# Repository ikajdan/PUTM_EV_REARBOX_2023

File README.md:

# Rearbox

This PCB integrates all rear-side vehicle electronics, handling communication, power outputs, and sensor inputs in a compact form factor.

<br>
<div align="center">
  </img>
  <br><br>
  <em>PCB layout.</em>
</div>
<br>

## Communication Interfaces

* **2× CAN transceivers** (external)
* **UART**, **SPI**, **I2C** (internal only)

## Power Outputs

* 2× fan drivers
* 2× pump drivers
* ASSI driver
* RTDS driver
* Brake light driver

## Sensor & Signal Inputs

* 12× digital safety inputs
* 2× suspension load cell sensors
* 2× suspension potentiometers
* 2× water pressure sensors
* 2× water temperature sensors
* Monocoque temperature sensors

## Overview

<br>
<div align="center">
  
&nbsp; &nbsp; &nbsp; &nbsp;
  
  <br><br>
  <em>Front and back view of the PCB.</em>
</div>
<br>

## Firmware

> [!IMPORTANT]
> For the CAN library to work correctly, the auto-generated HAL driver file needs to be patched.
>
> Make sure to restore any changes made by the generator to the `firmware/Drivers/STM32G4xx_HAL_Driver/Src/stm32g4xx_hal_fdcan.c` file or the receiving won't work!

Below are the changes that need to be made to the `stm32g4xx_hal_fdcan.c` file:

```diff
2231c2231
<     assert_param(IS_FDCAN_RX_FIFO(RxLocation));
---
>     //assert_param(IS_FDCAN_RX_FIFO(RxLocation));
2235c2235
<         if(RxLocation == FDCAN_RX_FIFO0) /* Rx element is assigned to the Rx FIFO 0 */
---
>         if(RxLocation == 0) /* Rx element is assigned to the Rx FIFO 0 */
2343c2343
<         if(RxLocation == FDCAN_RX_FIFO0) /* Rx element is assigned to the Rx FIFO 0 */
---
>         if(RxLocation == 0) /* Rx element is assigned to the Rx FIFO 0 */
```

## License

This project is licensed under the GPLv3 License. See the [LICENSE](LICENSE.md) file for details.

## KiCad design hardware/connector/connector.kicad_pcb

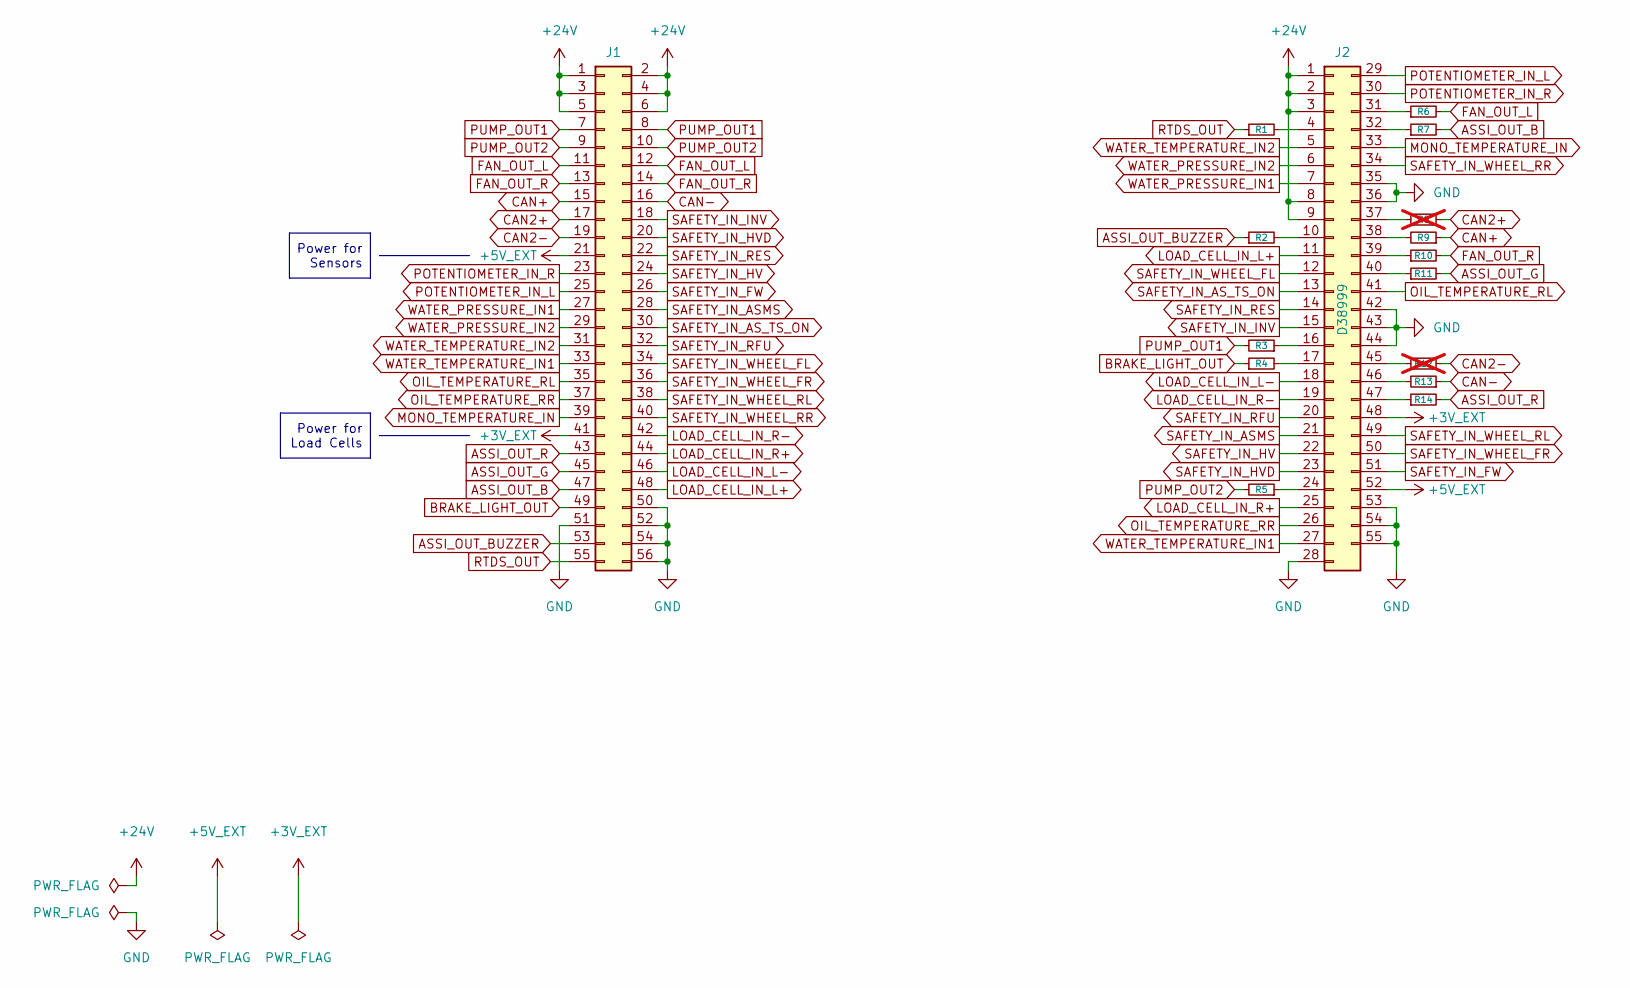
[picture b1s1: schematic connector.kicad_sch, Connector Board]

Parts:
J1: Conn_02x28_Top_Bottom; PinHeader_2x28_P2.00mm_Horizontal
J2: D38999; DTS20W17-35SN
R1, R2, R3, R4, R5, R6, R7, R9, R10, R11, R13, R14: 0R; R_0603_1608Metric
R8, R12: 0R; R_0603_1608Metric; not fitted

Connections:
+3V_EXT: J1.41, J2.48
+5V_EXT: J1.21, J2.52
+24V: J1.1, J1.2, J1.3, J1.4, J1.5, J1.6, J2.1, J2.2, J2.3, J2.8, J2.9
ASSI_OUT_B: J1.47, R7.2
ASSI_OUT_BUZZER: J1.53, R2.1
ASSI_OUT_G: J1.45, R11.2
ASSI_OUT_R: J1.43, R14.2
BRAKE_LIGHT_OUT: J1.49, R4.1
CAN2+: J1.17, R8.1
CAN2-: J1.19, R12.1
CAN+: J1.15, R9.1
CAN-: J1.16, R13.1
FAN_OUT_L: J1.11, J1.12, R6.2
FAN_OUT_R: J1.13, J1.14, R10.2
GND: J1.50, J1.51, J1.52, J1.54, J1.56, J2.28, J2.35, J2.36, J2.42, J2.43, J2.44, J2.53, J2.54, J2.55
LOAD_CELL_IN_L+: J1.48, J2.11
LOAD_CELL_IN_L-: J1.46, J2.18
LOAD_CELL_IN_R+: J1.44, J2.25
LOAD_CELL_IN_R-: J1.42, J2.19
MONO_TEMPERATURE_IN: J1.39, J2.33
unnamed: J2.4, R1.2
unnamed: J2.10, R2.2
unnamed: J2.16, R3.1
unnamed: J2.17, R4.2
unnamed: J2.24, R5.1
unnamed: J2.31, R6.1
unnamed: J2.32, R7.1
unnamed: J2.37, R8.2
unnamed: J2.38, R9.2
unnamed: J2.39, R10.1
unnamed: J2.40, R11.1
unnamed: J2.45, R12.2
unnamed: J2.46, R13.2
unnamed: J2.47, R14.1
OIL_TEMPERATURE_RL: J1.35, J2.41
OIL_TEMPERATURE_RR: J1.37, J2.26
POTENTIOMETER_IN_L: J1.25, J2.29
POTENTIOMETER_IN_R: J1.23, J2.30
PUMP_OUT1: J1.7, J1.8, R3.2
PUMP_OUT2: J1.9, J1.10, R5.2
RTDS_OUT: J1.55, R1.1
SAFETY_IN_ASMS: J1.28, J2.21
SAFETY_IN_AS_TS_ON: J1.30, J2.13
SAFETY_IN_FW: J1.26, J2.51
SAFETY_IN_HV: J1.24, J2.22
SAFETY_IN_HVD: J1.20, J2.23
SAFETY_IN_INV: J1.18, J2.15
SAFETY_IN_RES: J1.22, J2.14
SAFETY_IN_RFU: J1.32, J2.20
SAFETY_IN_WHEEL_FL: J1.34, J2.12
SAFETY_IN_WHEEL_FR: J1.36, J2.50
SAFETY_IN_WHEEL_RL: J1.38, J2.49
SAFETY_IN_WHEEL_RR: J1.40, J2.34
WATER_PRESSURE_IN1: J1.27, J2.7
WATER_PRESSURE_IN2: J1.29, J2.6
WATER_TEMPERATURE_IN1: J1.33, J2.27
WATER_TEMPERATURE_IN2: J1.31, J2.5

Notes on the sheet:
Power for Sensors
Power for Load Cells

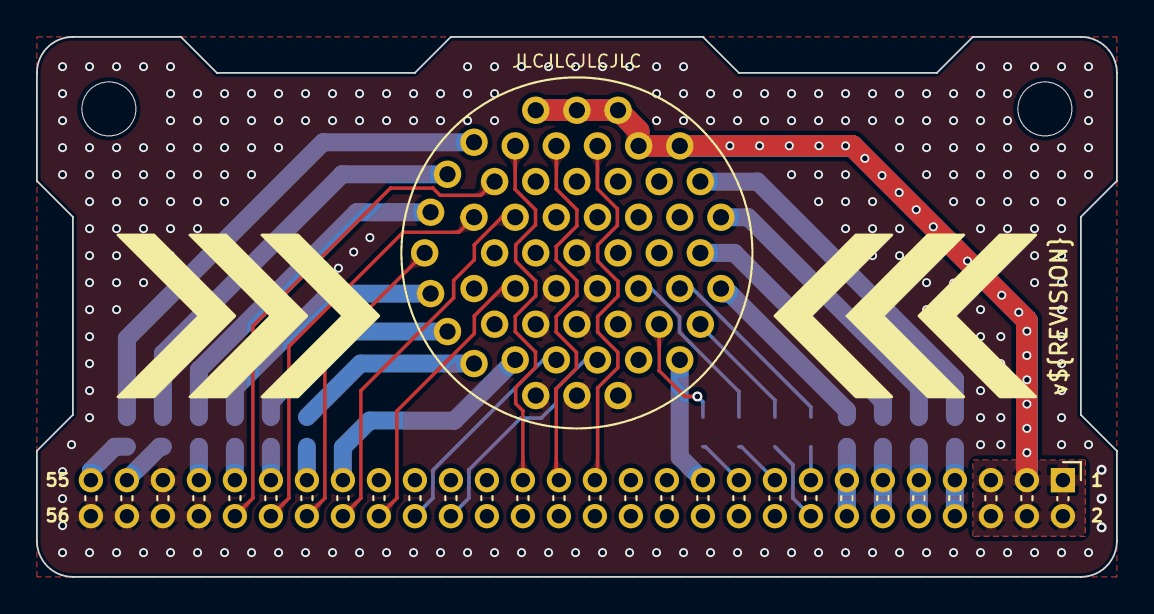
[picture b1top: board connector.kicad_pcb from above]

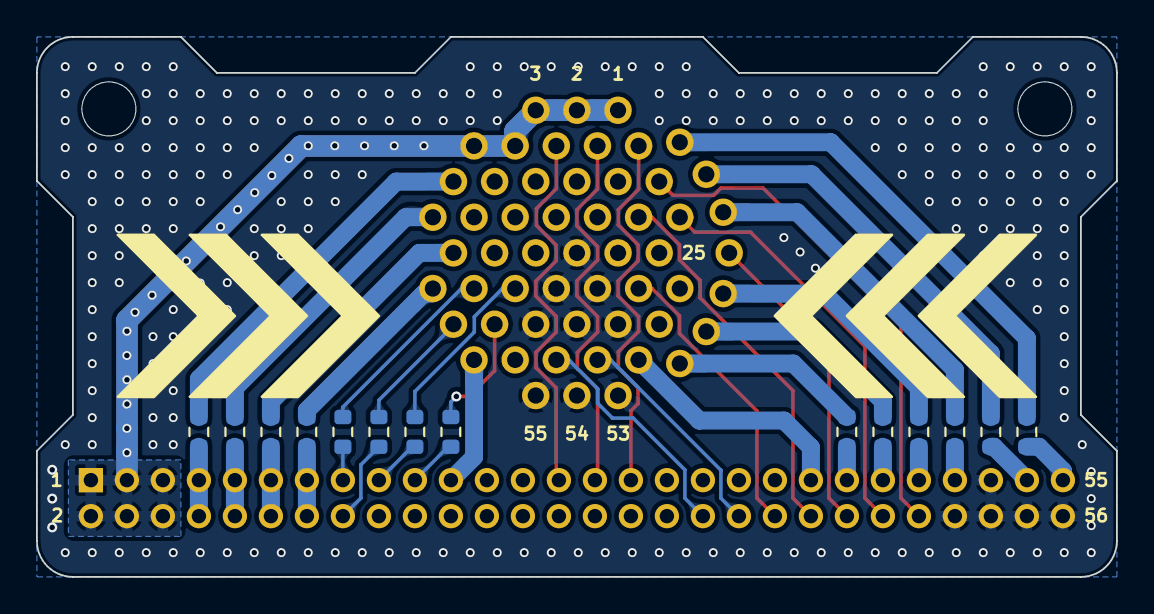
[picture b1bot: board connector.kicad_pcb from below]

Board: 4 copper layers, 60.0 x 30.0 mm, 16 parts (14 on the bottom side), 57 nets.

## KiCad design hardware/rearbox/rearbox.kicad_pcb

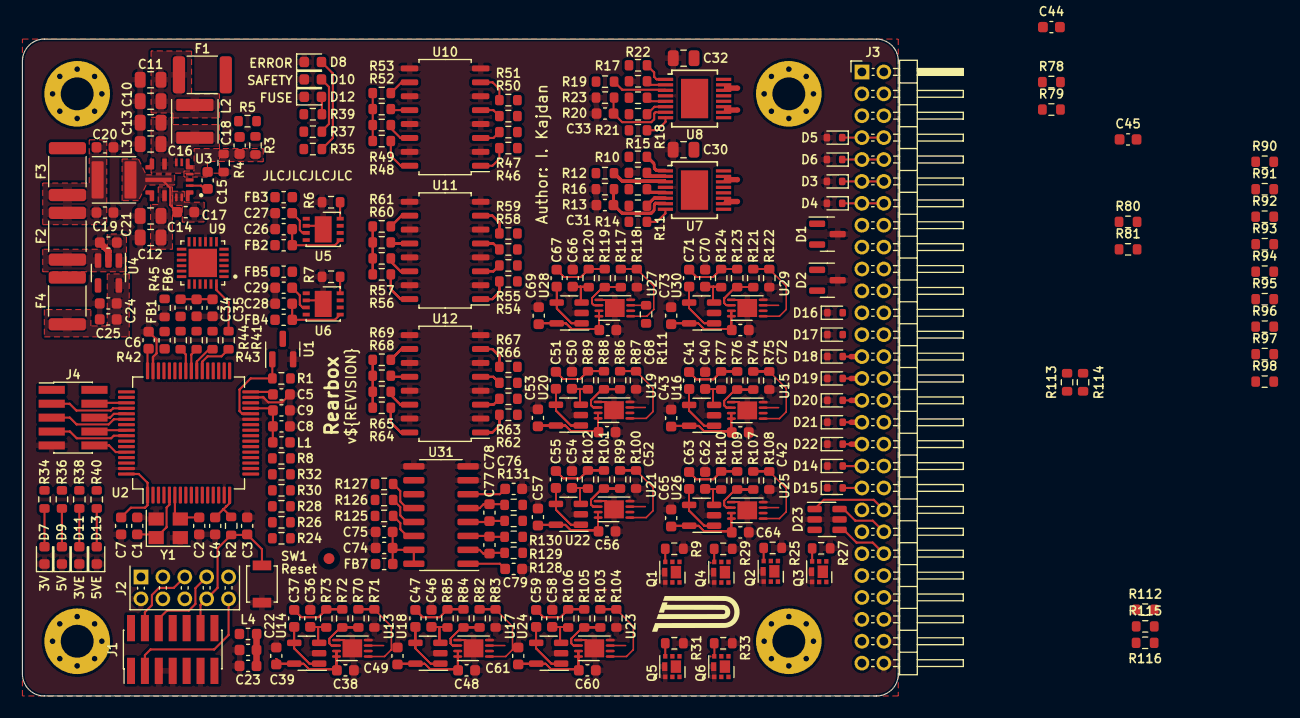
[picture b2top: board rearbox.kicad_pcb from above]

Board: 4 copper layers, 80.0 x 60.0 mm, 300 parts (0 on the bottom side), 227 nets.

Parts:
C1, C2: 10p; C_0603_1608Metric
C3, C4, C5, C6, C7, C9, C17, C23, C24, C26, C27, C28, C29, C35, C36, C37, C38, C39, C40, C41, C42, C43, C46, C47, C48, C49, C50, C51, C52, C53, C54, C55, C56, C57, C58, C59, C60, C61, C62, C63, C64, C65, C66, C67, C68, C69, C70, C71, C72, C73, C75, C76, C77, C78: 100n; C_0603_1608Metric
C8, C15, C21, C22, C25, C34, C74, C79: 1u; C_0603_1608Metric
C10, C11: 2u2; C_0805_2012Metric
C12, C13: 4u7; C_0805_2012Metric
C14, C16: 220n; C_0805_2012Metric
C18: 22p; C_0603_1608Metric
C19, C20: 22u; C_0603_1608Metric
C30, C32: 100n; C_0805_2012Metric
C31, C33, C44, C45: 10n; C_0603_1608Metric
D1, D2: PESD2CAN; SOT-23
D3, D4, D5, D6: PMEG3010EB; D_SOD-523
D7, D9, D11, D13: Green; LED_0603_1608Metric
D8, D10, D12: Red; LED_0603_1608Metric
D14, D15, D16, D17, D18, D19, D20, D21, D22: 5V; D_SOD-523
D23: CPDT6-5V4; SOT-23-6
F1: 1.5A; Fuse_1812_4532Metric
F2: 500mA; Fuse_1812_4532Metric
F3: 200mA; Fuse_1812_4532Metric
F4: 100mA; Fuse_1812_4532Metric
FB1, FB2, FB3, FB4, FB5, FB6, FB7: 470R; L_0603_1608Metric
J1: STDC14; PinHeader_2x07_P1.27mm_Vertical_SMD
J2: ST-LINK; STLINK-V3MINIE
J3: Conn_02x28_Top_Bottom; PinHeader_2x28_P2.00mm_Horizontal
J4: Auxiliary; PinHeader_2x05_P1.27mm_Vertical_SMD
L1, L4: 10u; L_0603_1608Metric
L2, L3: 1u5; L_Abracon_ASPI-4030S
NT1, NT2, NT3, NT4, NT5, NT6, NT7, NT8, NT9: NetTie_2; NetTie-2_SMD_Pad0.5mm
Q1, Q2, Q3, Q4, Q5, Q6: BUK6D210; Diodes_UDFN2020-6_Type-F
R1, R5, R90, R91, R92, R93, R95, R97: 1k; R_0603_1608Metric
R2, R9, R25, R27, R29, R31, R33, R48, R49, R52, R53, R56, R57, R60, R61, R64, R65, R68, R69: 10k; R_0603_1608Metric
R3: 100k; R_0603_1608Metric
R4: 24k9; R_0603_1608Metric
R6, R7, R45: 0R; R_0603_1608Metric
R8, R10, R11, R12, R13, R14, R17, R18, R19, R20, R21, R24, R26, R28, R30, R32, R41, R42, R43, R44, R79, R81, R125, R126, R127: 100R; R_0603_1608Metric
R15, R22: 15k; R_0603_1608Metric
R16, R23, R70, R71, R74, R75, R82, R83, R86, R87, R99, R100, R103, R104, R107, R108, R117, R118, R121, R122: TBD; R_0603_1608Metric
R34, R38: 82R; R_0603_1608Metric
R35, R37, R39: 120R; R_0603_1608Metric
R36, R40: 270R; R_0603_1608Metric
R46, R47, R50, R51, R54, R55, R58, R59, R62, R63, R66, R67: 2k; R_0603_1608Metric
R72, R73, R76, R77, R84, R85, R88, R89, R101, R102, R105, R106, R109, R110, R119, R120, R123, R124: 3k3; R_0603_1608Metric
R78, R80: 560R; R_0603_1608Metric
R94, R96, R98: 3k; R_0603_1608Metric
R111, R112, R113, R115: 50k; R_0603_1608Metric
R114, R116: 5k; R_0603_1608Metric
R128, R129, R130, R131: 51R; R_0603_1608Metric
SW1: Reset; SW_SPST_B3U-1000P
U1: LM4040C33FTA; SOT-23
U2: STM32G473RCTx; LQFP-64_10x10mm_P0.5mm
U3: LM62440-Q1; IC_LM61460AANRJRR
U4: TLV743P; SOT-23-5
U5, U6: MCP2542FD; DFN-8-1EP_3x3mm_P0.65mm_EP1.55x2.4mm
U7, U8: VND7020AJTR
U9: TCA6416ARTWR; QFN50P400X400X80-25N
U10, U11, U12: TLP291-4; SOIC-16_4.55x10.3mm_P1.27mm
U13, U15, U17, U19, U21, U23, U25, U27, U29: MCP6N11-005; TDFN-8-1EP_3x2mm_P0.5mm_EP1.80x1.65mm
U14, U16, U18, U20, U22, U24, U26, U28, U30: MCP6001; SOT-23-5
U31: NAU7802SGI; SOIC-16_3.9x9.9mm_P1.27mm
Y1: 48MHz; Crystal_SMD_Abracon_ABM8G-4Pin_3.2x2.5mm

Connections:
+3.3V: C24.1, C25.1, F4.1, FB1.2, FB2.1, FB4.1, FB6.1, FB7.1, J4.1, L1.1, L4.1, R34.1, R48.2, R49.2, R52.2, R53.2, R56.2, R57.2, R60.2, R61.2, R64.2, R65.2, R68.2, R69.2, U4.5 (OUT)
+3.3VA: C22.1, C23.1, C38.1, C39.1, C42.1, C43.1, C48.1, C49.1, C52.1, C53.1, C56.1, C57.1, C60.1, C61.1, C64.1, C65.1, C68.1, C69.1, C72.1, C73.1, L4.2, R78.1, R80.1, U13.7 (V+), U13.8 (EN), U14.5 (V+), U15.7 (V+), U15.8 (EN), U16.5 (V+), U17.7 (V+), U17.8 (EN), U18.5 (V+), U19.7 (V+), U19.8 (EN), U20.5 (V+), U21.7 (V+), U21.8 (EN), U22.5 (V+), U23.7 (V+), U23.8 (EN), U24.5 (V+), U25.7 (V+), U25.8 (EN), U26.5 (V+), U27.7 (V+), U27.8 (EN), U28.5 (V+), U29.7 (V+), U29.8 (EN), U30.5 (V+)
+3V_EXT: C79.1, F4.2, J3.41, R38.1, U31.1 (REFP)
+5V: C19.1, C20.1, F2.1, F3.1, FB3.1, FB5.1, J4.2, L3.2, R1.1, R3.1, R5.1, R36.1, U3.1 (BIAS)
+5V_EXT: F3.2, J3.21, R40.1, R90.1, R91.1, R92.1, R93.1, R95.1, R97.1, R111.1, R112.1, R113.1, R115.1
+24V: C30.1, C32.1, F1.1, J3.1, J3.2, J3.3, J3.4, J3.5, J3.6, U7.EPAD (VCC), U8.EPAD (VCC)
/ANALOG_INPUT1: C37.2, U2.20 (PA6), U14.1, U14.4 (-)
/ANALOG_INPUT2: C41.2, U2.21 (PA7), U16.1, U16.4 (-)
/ANALOG_OFFSET1: U2.18 (PA4), U13.2 (-)
/ANALOG_OFFSET2: U2.19 (PA5), U15.2 (-)
/ASSI_BUZZER: R30.2, U2.4 (PC15)
/ASSI_LED_B: R28.2, U2.17 (PA3)
/ASSI_LED_G: R26.2, U2.9 (PC1)
/ASSI_LED_R: R24.2, U2.8 (PC0)
/BRAKE_LIGHT: R8.2, U2.2 (PC13)
/CAN2_RX: U2.34 (PB12), U6.4 (RXD)
/CAN2_TX: U2.35 (PB13), U6.1 (TXD)
/CAN_RX: U2.45 (PA11), U5.4 (RXD)
/CAN_TX: U2.46 (PA12), U5.1 (TXD)
/FAN_L: R10.1, U2.37 (PB15)
/FAN_R: R11.1, U2.36 (PB14)
/HSE_IN: C1.1, U2.5 (PF0), Y1.1
/HSE_OUT: C2.1, U2.6 (PF1), Y1.3
/LED_ERROR: R35.1, U9.6 (P05)
/LED_FUSE: R39.1, U9.8 (P07)
/LED_SAFETY: R37.1, U9.7 (P06)
/LOAD_CELL_DRDY: R127.1, U2.44 (PA10)
/LOAD_CELL_SCLK: R126.1, U2.43 (PA9)
/LOAD_CELL_SDIO: R125.1, U2.42 (PA8)
/MONO_TEMPERATURE: C63.2, U2.10 (PC2), U26.1, U26.4 (-)
/POTENTIOMETER_L: C67.2, U2.22 (PC4), U28.1, U28.4 (-)
/POTENTIOMETER_R: C71.2, U2.23 (PC5), U30.1, U30.4 (-)
/PUMP1: R17.1, U2.33 (PB11)
/PUMP2: R18.1, U2.30 (PB10)
/Power Supply/+5V_FUSED: C21.1, F2.2, U4.1 (IN), U4.3 (EN)
/Power Supply/+24V_FUSED: C10.1, C11.1, F1.2, L2.1
/Power Supply/FB: C18.2, R3.2, R4.1, U3.4 (FB)
/Power Supply/SW: C17.1, L3.1, U3.10 (SW)
/Power Supply/VIN: C12.1, C13.1, C14.1, C16.1, L2.2, U3.7 (EN), U3.8 (VIN1), U3.12 (VIN2)
/RTDS: R32.2, U2.3 (PC14)
/SAFETY_SCL: R43.1, U2.40 (PC8)
/SAFETY_SDA: R42.1, U2.41 (PC9)
/SAFETY_~INT: R44.1, U2.39 (PC7)
/SAFETY_~RESET: R41.1, U2.38 (PC6)
/SENSE_ADDRESS_IN0: R13.1, R20.1, U2.25 (PB1)
/SENSE_ADDRESS_IN1: R14.1, R21.1, U2.26 (PB2)
/SENSE_ENABLE_FANS: R12.1, U2.59 (PB6)
/SENSE_ENABLE_PUMPS: R19.1, U2.58 (PB5)
/SENSE_OUT: C31.1, C33.1, R16.1, R23.1, U2.24 (PB0), U7.7 (MultiSense), U8.7 (MultiSense)
/Safety Inputs/OUT_ASMS: R65.1, U9.15, U12.14
/Safety Inputs/OUT_FW: R48.1, U9.1 (P00), U10.16
/Safety Inputs/OUT_HV: R49.1, U9.2 (P01), U10.14
/Safety Inputs/OUT_HVD: R53.1, U9.4 (P03), U10.10
/Safety Inputs/OUT_INV: R52.1, U9.3 (P02), U10.12
/Safety Inputs/OUT_RES: R64.1, U9.14, U12.16
/Safety Inputs/OUT_RFU1: R68.1, U9.16, U12.12
/Safety Inputs/OUT_RFU2: R69.1, U9.17, U12.10
/Safety Inputs/OUT_W_FL: R56.1, U9.10, U11.16
/Safety Inputs/OUT_W_FR: R57.1, U9.11, U11.14
/Safety Inputs/OUT_W_RL: R60.1, U9.12, U11.12
/Safety Inputs/OUT_W_RR: R61.1, U9.13, U11.10
/Safety Inputs/TCA_VDD: C34.1, C35.1, FB6.2, U9.21 (VCCP), U9.23 (VCCI)
/Suspension Load Cells/NAU_VDD: C74.1, C75.1, FB7.2, U31.15 (DVDD), U31.16 (AVDD)
/Suspension Potentiometers/N1: R113.2, R114.1, U27.2 (-)
/Suspension Potentiometers/N2: R115.2, R116.1, U29.2 (-)
/Suspension Potentiometers/P1: D21.2 (A2), NT8.2, R111.2, U27.3 (+)
/Suspension Potentiometers/P2: D22.2 (A2), NT9.2, R112.2, U29.3 (+)
/Temperature Sensors/N1: R93.2, R94.1, U21.2 (-)
/Temperature Sensors/N2: R95.2, R96.1, U23.2 (-)
/Temperature Sensors/N3: R97.2, R98.1, U25.2 (-)
/Temperature Sensors/P1: D18.2 (A2), NT5.2, R90.2, U21.3 (+)
/Temperature Sensors/P2: D19.2 (A2), NT6.2, R91.2, U23.3 (+)
/Temperature Sensors/P3: D20.2 (A2), NT7.2, R92.2, U25.3 (+)
/VREF: R1.2, U1.1 (K), U2.28 (VREF+)
/WATER_PRESSURE1: C47.2, U2.13 (PA1), U18.1, U18.4 (-)
/WATER_PRESSURE2: C51.2, U2.14 (PA2), U20.1, U20.4 (-)
/WATER_TEMPERATURE1: C55.2, U2.11 (PC3), U22.1, U22.4 (-)
/WATER_TEMPERATURE2: C59.2, U2.12 (PA0), U24.1, U24.4 (-)
/Water Pressure Sensors/Analog Input 3/-: C44.1, R78.2, R79.1, U17.2 (-)
/Water Pressure Sensors/Analog Input 4/-: C45.1, R80.2, R81.1, U19.2 (-)
ANALOG_IN_RFU1: D14.2 (A2), J3.37, U13.3 (+)
ANALOG_IN_RFU2: D15.2 (A2), J3.39, U15.3 (+)
ASSI_OUT_B: J3.47, Q4.1 (D), Q4.2 (D), Q4.5 (D), Q4.6 (D), Q4.7 (D)
ASSI_OUT_BUZZER: J3.53, Q5.1 (D), Q5.2 (D), Q5.5 (D), Q5.6 (D), Q5.7 (D)
ASSI_OUT_G: J3.45, Q3.1 (D), Q3.2 (D), Q3.5 (D), Q3.6 (D), Q3.7 (D)
ASSI_OUT_R: J3.43, Q2.1 (D), Q2.2 (D), Q2.5 (D), Q2.6 (D), Q2.7 (D)
BRAKE_LIGHT_OUT: J3.49, Q1.1 (D), Q1.2 (D), Q1.5 (D), Q1.6 (D), Q1.7 (D)
CAN2+: D2.1 (A1), J3.17, U6.7 (CANH)
CAN2-: D2.2 (A2), J3.19, U6.6 (CANL)
CAN+: D1.1 (A1), J3.15, U5.7 (CANH)
CAN-: D1.2 (A2), J3.16, U5.6 (CANL)
FAN_OUT_L: D3.1 (K), J3.11, J3.12, NT1.1, NT1.2, U7.13 (OUTPUT0), U7.14 (OUTPUT0), U7.15 (OUTPUT0), U7.16 (OUTPUT0)
FAN_OUT_R: D4.1 (K), J3.13, J3.14, NT2.1, NT2.2, U7.9 (OUTPUT1), U7.10 (OUTPUT1), U7.11 (OUTPUT1), U7.12 (OUTPUT1)
GND: C1.2, C2.2, C3.2, C4.2, C5.2, C6.2, C7.2, C8.2, C9.2, C10.2, C11.2, C12.2, C13.2, C14.2, C15.2, C16.2, C19.2, C20.2, C21.2, C22.2, C23.2, C24.2, C25.2, C26.2, C27.2, C28.2, C29.2, C30.2, C31.2, C32.2, C33.2, C34.2, C35.2, C36.2, C38.2, C39.2, C40.2, C42.2, C43.2, C44.2, C45.2, C46.2, C48.2, C49.2, C50.2, C52.2, C53.2, C54.2, C56.2, C57.2, C58.2, C60.2, C61.2, C62.2, C64.2, C65.2, C66.2, C68.2, C69.2, C70.2, C72.2, C73.2, C74.2, C75.2, C76.2, C79.2, D1.3 (common), D2.3 (common), D3.2 (A), D4.2 (A), D5.2 (A), D6.2 (A), D7.1 (K), D8.1 (K), D9.1 (K), D10.1 (K), D11.1 (K), D12.1 (K), D13.1 (K), D14.1 (A1), D15.1 (A1), D16.1 (A1), D17.1 (A1), D18.1 (A1), D19.1 (A1), D20.1 (A1), D21.1 (A1), D22.1 (A1), D23.2 (D2), D23.5 (A5), J1.5, J1.7, J1.11, J2.6 (GND), J3.50, J3.51, J3.52, J3.54, J3.56, J4.9, Q1.4 (S), Q1.8 (S), Q2.4 (S), Q2.8 (S), Q3.4 (S), Q3.8 (S), Q4.4 (S), Q4.8 (S), Q5.4 (S), Q5.8 (S), Q6.4 (S), Q6.8 (S), R4.2, R6.1, R7.1, R9.1, R15.2, R16.2, R22.2, R23.2, R25.1, R27.1, R29.1, R31.1, R33.1, R45.1, R71.1, R75.1, R79.2, R81.2, R83.1, R87.1, R94.2, R96.2, R98.2, R100.1, R104.1, R108.1, R114.2, R116.2, R118.1, R122.1, SW1.1, U1.2 (A), U2.15 (VSS), U2.27 (VSSA), U2.31 (VSS), U2.47 (VSS), U2.63 (VSS), U3.3 (AGND), U3.6 (MODE/SYNC), U3.9 (PGND1), U3.11 (PGND2), U4.2 (GND), U5.2 (VSS), U5.9 (VSS), U6.2 (VSS), U6.9 (VSS), U7.4 (GND), U8.4 (GND), U9.9 (GND), U9.25 (EP), U10.2, U10.4, U10.6, U10.8, U10.9, U10.11, U10.13, U10.15, U11.2, U11.4, U11.6, U11.8, U11.9, U11.11, U11.13, U11.15, U12.2, U12.4, U12.6, U12.8, U12.9, U12.11, U12.13, U12.15, U13.4 (V-), U13.5 (RF), U13.9 (EP), U14.2 (V-), U15.4 (V-), U15.5 (RF), U15.9 (EP), U16.2 (V-), U17.4 (V-), U17.5 (RF), U17.9 (EP), U18.2 (V-), U19.4 (V-), U19.5 (RF), U19.9 (EP), U20.2 (V-), U21.4 (V-), U21.5 (RF), U21.9 (EP), U22.2 (V-), U23.4 (V-), U23.5 (RF), U23.9 (EP), U24.2 (V-), U25.4 (V-), U25.5 (RF), U25.9 (EP), U26.2 (V-), U27.4 (V-), U27.5 (RF), U27.9 (EP), U28.2 (V-), U29.4 (V-), U29.5 (RF), U29.9 (EP), U30.2 (V-), U31.7 (REFN), U31.8 (AVSS), U31.9 (DVSS), Y1.2, Y1.4
I^{2}C_SCL: J4.4, U2.51 (PA15)
I^{2}C_SDA: J4.10, U2.60 (PB7)
LOAD_CELL_IN_L+: D23.1 (A1), J3.42, R128.2
LOAD_CELL_IN_L-: D23.6 (D6), J3.44, R129.2
LOAD_CELL_IN_R+: D23.4 (C4), J3.46, R130.2
LOAD_CELL_IN_R-: D23.3 (B3), J3.48, R131.2
MONO_TEMPERATURE_IN: J3.31, NT7.1
NRST: C3.1, J1.12, J2.9 (T_NRST), R2.2, SW1.2, U2.7 (PG10)
unnamed: C18.1, R5.2
unnamed: C37.1, R72.2, R73.1
unnamed: C41.1, R76.2, R77.1
unnamed: C47.1, R84.2, R85.1
unnamed: C51.1, R88.2, R89.1
unnamed: C55.1, R101.2, R102.1
unnamed: C59.1, R105.2, R106.1
unnamed: C63.1, R109.2, R110.1
unnamed: C67.1, R119.2, R120.1
unnamed: C71.1, R123.2, R124.1
unnamed: D7.2 (A), R34.2
unnamed: D8.2 (A), R35.2
unnamed: D9.2 (A), R36.2
unnamed: D10.2 (A), R37.2
unnamed: D11.2 (A), R38.2
unnamed: D12.2 (A), R39.2
unnamed: D13.2 (A), R40.2
unnamed: Q1.3 (G), R8.1, R9.2
unnamed: Q2.3 (G), R24.1, R25.2
unnamed: Q3.3 (G), R26.1, R27.2
unnamed: Q4.3 (G), R28.1, R29.2
unnamed: Q5.3 (G), R30.1, R31.2
unnamed: Q6.3 (G), R32.1, R33.2
unnamed: R46.2, U10.1
unnamed: R47.2, U10.3
unnamed: R50.2, U10.5
unnamed: R51.2, U10.7
unnamed: R54.2, U11.1
unnamed: R55.2, U11.3
unnamed: R58.2, U11.5
unnamed: R59.2, U11.7
unnamed: R62.2, U12.1
unnamed: R63.2, U12.3
unnamed: R66.2, U12.5
unnamed: R67.2, U12.7
unnamed: R70.2, R72.1, U13.6
unnamed: R74.2, R76.1, U15.6
unnamed: R82.2, R84.1, U17.6
unnamed: R86.2, R88.1, U19.6
unnamed: R99.2, R101.1, U21.6
unnamed: R103.2, R105.1, U23.6
unnamed: R107.2, R109.1, U25.6
unnamed: R117.2, R119.1, U27.6
unnamed: R121.2, R123.1, U29.6
unnamed: C17.2, U3.13 (RBOOT), U3.14 (CBOOT)
unnamed: C15.1, U3.2 (VCC)
unnamed: R6.2, U5.8 (STBY)
unnamed: C27.1, FB3.2, U5.3 (VDD)
unnamed: C26.1, FB2.2, U5.5 (VIO)
unnamed: R7.2, U6.8 (STBY)
unnamed: C29.1, FB5.2, U6.3 (VDD)
unnamed: C28.1, FB4.2, U6.5 (VIO)
unnamed: R10.2, U7.1 (INPUT0)
unnamed: R11.2, U7.8 (INPUT1)
unnamed: R13.2, U7.5 (SEL0)
unnamed: R14.2, U7.6 (SEL1)
unnamed: R12.2, U7.3 (SEn)
unnamed: R15.1, U7.2 (~FaultRST)
unnamed: R17.2, U8.1 (INPUT0)
unnamed: R18.2, U8.8 (INPUT1)
unnamed: R20.2, U8.5 (SEL0)
unnamed: R21.2, U8.6 (SEL1)
unnamed: R19.2, U8.3 (SEn)
unnamed: R22.1, U8.2 (~FaultRST)
unnamed: R45.2, U9.18 (ADDR)
unnamed: R43.2, U9.19 (SCL)
unnamed: R42.2, U9.20 (SDA)
unnamed: R44.2, U9.22 (~INT)
unnamed: R41.2, U9.24 (~RESET)
unnamed: R70.1, R71.2, U13.1 (FG)
unnamed: C36.1, R73.2, U14.3 (+)
unnamed: R74.1, R75.2, U15.1 (FG)
unnamed: C40.1, R77.2, U16.3 (+)
unnamed: R82.1, R83.2, U17.1 (FG)
unnamed: C46.1, R85.2, U18.3 (+)
unnamed: R86.1, R87.2, U19.1 (FG)
unnamed: C50.1, R89.2, U20.3 (+)
unnamed: R99.1, R100.2, U21.1 (FG)
unnamed: C54.1, R102.2, U22.3 (+)
unnamed: R103.1, R104.2, U23.1 (FG)
unnamed: C58.1, R106.2, U24.3 (+)
unnamed: R107.1, R108.2, U25.1 (FG)
unnamed: C62.1, R110.2, U26.3 (+)
unnamed: R117.1, R118.2, U27.1 (FG)
unnamed: C66.1, R120.2, U28.3 (+)
unnamed: R121.1, R122.2, U29.1 (FG)
unnamed: C70.1, R124.2, U30.3 (+)
unnamed: R127.2, U31.12 (DRDY)
unnamed: R126.2, U31.13 (SCLK)
unnamed: R125.2, U31.14 (SDIO)
unnamed: C76.1, U31.6 (VBG)
unnamed: C77.1, R128.1, U31.2 (VIN1N)
unnamed: C77.2, R129.1, U31.3 (VIN1P)
unnamed: C78.1, R130.1, U31.4 (VIN2N)
unnamed: C78.2, R131.1, U31.5 (VIN2P)
POTENTIOMETER_IN_L: J3.33, NT8.1
POTENTIOMETER_IN_R: J3.35, NT9.1
PUMP_OUT1: D5.1 (K), J3.7, J3.8, NT3.1, NT3.2, U8.13 (OUTPUT0), U8.14 (OUTPUT0), U8.15 (OUTPUT0), U8.16 (OUTPUT0)
PUMP_OUT2: D6.1 (K), J3.9, J3.10, NT4.1, NT4.2, U8.9 (OUTPUT1), U8.10 (OUTPUT1), U8.11 (OUTPUT1), U8.12 (OUTPUT1)
RTDS_OUT: J3.55, Q6.1 (D), Q6.2 (D), Q6.5 (D), Q6.6 (D), Q6.7 (D)
SAFETY_IN_ASMS: J3.28, R63.1
SAFETY_IN_FW: J3.26, R46.1
SAFETY_IN_HV: J3.24, R47.1
SAFETY_IN_HVD: J3.20, R51.1
SAFETY_IN_INV: J3.18, R50.1
SAFETY_IN_RES: J3.22, R62.1
SAFETY_IN_RFU1: J3.30, R66.1
SAFETY_IN_RFU2: J3.32, R67.1
SAFETY_IN_WHEEL_FL: J3.34, R54.1
SAFETY_IN_WHEEL_FR: J3.36, R55.1
SAFETY_IN_WHEEL_RL: J3.38, R58.1
SAFETY_IN_WHEEL_RR: J3.40, R59.1
SPI_MISO: J4.7, U2.57 (PB4)
SPI_MOSI: J4.5, U2.54 (PC12)
SPI_SCLK: J4.8, U2.56 (PB3)
SWCLK: J1.6, J2.4 (T_JCLK/T_SWCLK), U2.50 (PA14)
SWDIO: J1.4, J2.3 (T_JTMS/T_SWDIO), U2.49 (PA13)
UART_RX: J4.6, U2.53 (PC11)
UART_TX: J4.3, U2.52 (PC10)
VDD: C4.1, C5.1, C6.1, C7.1, FB1.1, J1.3, J2.10 (T_VCC), R2.1, U2.1 (VBAT), U2.16 (VDD), U2.32 (VDD), U2.48 (VDD), U2.64 (VDD)
VDDA: C8.1, C9.1, L1.2, U2.29 (VDDA)
WATER_PRESSURE_IN1: D16.2 (A2), J3.23, U17.3 (+)
WATER_PRESSURE_IN2: D17.2 (A2), J3.25, U19.3 (+)
WATER_TEMPERATURE_IN1: J3.27, NT5.1
WATER_TEMPERATURE_IN2: J3.29, NT6.1

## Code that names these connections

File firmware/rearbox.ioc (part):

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Mcu.Name=STM32G473R(B-C-E)Tx
Mcu.Package=LQFP64
Mcu.UserName=STM32G473RCTx
PA0.GPIOParameters=GPIO_Label
PA0.GPIO_Label=WATER_TEMPERATURE2
PA0.Mode=IN1-Single-Ended
PA0.Signal=ADC1_IN1
PA1.GPIOParameters=GPIO_Label
PA1.GPIO_Label=WATER_PRESSURE1
PA1.Mode=IN2-Single-Ended
PA1.Signal=ADC1_IN2
PA10.GPIOParameters=GPIO_Label
PA10.GPIO_Label=LOAD_CELL_DRDY
PA10.Signal=GPXTI10
PA11.GPIOParameters=GPIO_Label
PA11.GPIO_Label=CAN_RX
PA11.Mode=FDCAN_Activate
PA11.Signal=FDCAN1_RX
PA12.GPIOParameters=GPIO_Label
PA12.GPIO_Label=CAN_TX
PA12.Mode=FDCAN_Activate
PA12.Signal=FDCAN1_TX
PA13.GPIOParameters=GPIO_Label
PA13.GPIO_Label=SWDIO
PA13.Mode=Serial_Wire
PA13.Signal=SYS_JTMS-SWDIO
PA14.GPIOParameters=GPIO_Label
PA14.GPIO_Label=SWCLK
PA14.Mode=Serial_Wire
PA14.Signal=SYS_JTCK-SWCLK
PA15.GPIOParameters=GPIO_Label
PA15.GPIO_Label=I2C_SCL
PA15.Mode=I2C
PA15.Signal=I2C1_SCL
PA2.GPIOParameters=GPIO_Label
PA2.GPIO_Label=WATER_PRESSURE2
PA2.Mode=IN3-Single-Ended
PA2.Signal=ADC1_IN3
PA3.GPIOParameters=GPIO_Label
PA3.GPIO_Label=ASSI_LED_B
PA3.Signal=GPIO_Output
PA4.GPIOParameters=GPIO_Label
PA4.GPIO_Label=ANALOG_OFFSET1
PA4.Signal=COMP_DAC11_group
PA5.GPIOParameters=GPIO_Label
PA5.GPIO_Label=ANALOG_OFFSET2
PA5.Signal=COMP_DAC12_group
PA6.GPIOParameters=GPIO_Label
PA6.GPIO_Label=ANALOG_INPUT1
PA6.Mode=IN3-Single-Ended
PA6.Signal=ADC2_IN3
PA7.GPIOParameters=GPIO_Label
PA7.GPIO_Label=ANALOG_INPUT2
PA7.Mode=IN4-Single-Ended
PA7.Signal=ADC2_IN4
PA8.GPIOParameters=GPIO_Label
PA8.GPIO_Label=LOAD_CELL_SDIO
PA8.Mode=I2C
PA8.Signal=I2C2_SDA
PA9.GPIOParameters=GPIO_Label
PA9.GPIO_Label=LOAD_CELL_SCLK
PA9.Mode=I2C
PA9.Signal=I2C2_SCL
PB0.GPIOParameters=GPIO_Label
PB0.GPIO_Label=SENSE_OUT
PB0.Mode=IN15-Single-Ended
PB0.Signal=ADC1_IN15
PB1.GPIOParameters=GPIO_Label
PB1.GPIO_Label=SENSE_ADDRESS_IN0
PB1.Signal=GPIO_Output
PB10.GPIOParameters=GPIO_Label
PB10.GPIO_Label=PUMP2
PB10.Signal=S_TIM2_CH3
PB11.GPIOParameters=GPIO_Label
PB11.GPIO_Label=PUMP1
PB11.Signal=S_TIM2_CH4
PB12.GPIOParameters=GPIO_Label
PB12.GPIO_Label=CAN2_RX
PB12.Signal=FDCAN2_RX
PB13.GPIOParameters=GPIO_Label
PB13.GPIO_Label=CAN2_TX
PB13.Signal=FDCAN2_TX
PB14.GPIOParameters=GPIO_Label
PB14.GPIO_Label=FAN_R
PB14.Signal=S_TIM15_CH1
PB15.GPIOParameters=GPIO_Label
PB15.GPIO_Label=FAN_L
PB15.Signal=S_TIM15_CH2
PB2.GPIOParameters=GPIO_Label
PB2.GPIO_Label=SENSE_ADDRESS_IN1
PB2.Signal=GPIO_Output
PB3.GPIOParameters=GPIO_Label
PB3.GPIO_Label=SPI_SCLK
PB3.Mode=Full_Duplex_Master
PB3.Signal=SPI3_SCK
PB4.GPIOParameters=GPIO_Label
PB4.GPIO_Label=SPI_MISO
PB4.Mode=Full_Duplex_Master
PB4.Signal=SPI3_MISO
PB5.GPIOParameters=GPIO_Label
PB5.GPIO_Label=SENSE_ENABLE_PUMPS
PB5.Signal=GPIO_Output
PB6.GPIOParameters=GPIO_Label
PB6.GPIO_Label=SENSE_ENABLE_FANS
PB6.Signal=GPIO_Output
PB7.GPIOParameters=GPIO_Label
PB7.GPIO_Label=I2C_SDA
PB7.Mode=I2C
PB7.Signal=I2C1_SDA
PB8-BOOT0.GPIOParameters=GPIO_Label
PB8-BOOT0.GPIO_Label=BOOT_SELECT
PB8-BOOT0.Signal=GPIO_Output
PC0.GPIOParameters=GPIO_Label
PC0.GPIO_Label=ASSI_LED_R
PC0.Signal=GPIO_Output
PC1.GPIOParameters=GPIO_Label
PC1.GPIO_Label=ASSI_LED_G
PC1.Signal=GPIO_Output
PC10.GPIOParameters=GPIO_Label
PC10.GPIO_Label=UART_TX
PC10.Mode=Asynchronous
PC10.Signal=USART3_TX
PC11.GPIOParameters=GPIO_Label
PC11.GPIO_Label=UART_RX
PC11.Mode=Asynchronous
PC11.Signal=USART3_RX
PC12.GPIOParameters=GPIO_Label
PC12.GPIO_Label=SPI_MOSI
PC12.Mode=Full_Duplex_Master
PC12.Signal=SPI3_MOSI
PC13.GPIOParameters=GPIO_Label
PC13.GPIO_Label=BRAKE_LIGHT
PC13.Signal=GPIO_Output
PC14-OSC32_IN.GPIOParameters=GPIO_Label
PC14-OSC32_IN.GPIO_Label=RTDS
PC14-OSC32_IN.Signal=GPIO_Output
PC15-OSC32_OUT.GPIOParameters=GPIO_Label
PC15-OSC32_OUT.GPIO_Label=ASSI_BUZZER
PC15-OSC32_OUT.Signal=GPIO_Output
PC2.GPIOParameters=GPIO_Label
PC2.GPIO_Label=MONO_TEMPERATURE
PC2.Mode=IN8-Single-Ended
PC2.Signal=ADC1_IN8
PC3.GPIOParameters=GPIO_Label
PC3.GPIO_Label=WATER_TEMPERATURE1
PC3.Mode=IN9-Single-Ended
PC3.Signal=ADC1_IN9
PC4.GPIOParameters=GPIO_Label
PC4.GPIO_Label=POTENTIOMETER_L
PC4.Mode=IN5-Single-Ended
PC4.Signal=ADC2_IN5
PC5.GPIOParameters=GPIO_Label
PC5.GPIO_Label=POTENTIOMETER_R
PC5.Mode=IN11-Single-Ended
PC5.Signal=ADC2_IN11
PC6.GPIOParameters=PinState,GPIO_PuPd,GPIO_Label
PC6.GPIO_Label=SAFETY_RESET
PC6.GPIO_PuPd=GPIO_PULLUP
PC6.PinState=GPIO_PIN_SET
PC6.Signal=GPIO_Output
PC7.GPIOParameters=GPIO_PuPd,GPIO_Label,GPIO_ModeDefaultEXTI
PC7.GPIO_Label=SAFETY_INT
PC7.GPIO_ModeDefaultEXTI=GPIO_MODE_IT_FALLING
PC7.GPIO_PuPd=GPIO_PULLUP
PC7.Signal=GPXTI7
PC8.GPIOParameters=GPIO_Label,GPIO_Pu
PC8.GPIO_Label=SAFETY_SCL
PC8.GPIO_Pu=GPIO_PULLUP
PC8.Mode=I2C
PC8.Signal=I2C3_SCL
PC9.GPIOParameters=GPIO_Label,GPIO_Pu
PC9.GPIO_Label=SAFETY_SDA
PC9.GPIO_Pu=GPIO_PULLUP
PC9.Mode=I2C
PC9.Signal=I2C3_SDA
PF0-OSC_IN.GPIOParameters=GPIO_Label
PF0-OSC_IN.GPIO_Label=HSE_IN
PF0-OSC_IN.Mode=HSE-External-Oscillator
PF0-OSC_IN.Signal=RCC_OSC_IN
PF1-OSC_OUT.GPIOParameters=GPIO_Label
PF1-OSC_OUT.GPIO_Label=HSE_OUT
PF1-OSC_OUT.Mode=HSE-External-Oscillator
PF1-OSC_OUT.Signal=RCC_OSC_OUT
RCC.HSE_VALUE=48000000
RCC.SYSCLKFreq_VALUE=160000000
RCC.SYSCLKSource=RCC_SYSCLKSOURCE_PLLCLK
board=custom

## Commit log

2023-04-24 Generate KiCad project from the template
2023-06-08 Add components
2023-07-01 Add the Cube project
2023-07-07 Improve the schematic
    - add anti-aliasing filters
    - rearrange the main connector signals
    - improve the power filtering
2023-07-28 Set component values
2023-07-28 Number subsheets in order
2023-09-19 Improve the schematic according to the feedback
2023-09-23 Add high-side drivers to the fans and pumps
2023-09-23 Use in-amps
2023-10-03 Improve the diagram based on the feedback
    - add an input LC filter
    - remove the USB connector
    - add a programmer connector
    - move optocouplers into a subsheet
    - add a suspension tension meter IC
2023-10-03 Add the connector board
2023-11-02 Place components on the PCB
2023-11-07 Align footprint references
2023-11-16 Route PCB tracks
2023-11-17 Fix DRCs
2023-11-17 Add teardrops
2023-11-17 Improve the routing of pump drivers and CAN buses
2023-11-17 Adjust vias
2023-11-17 Update component description
2024-02-13 Add pwm, adc and VND7020AJ components
2024-02-13 Route the tracks on the connector PCB
2024-02-20 Add the connector model
2024-03-04 Add TCA driver
2024-03-04 Implement control loop
2024-03-13 Implement analog functions
2024-04-28 Fix measurement bridges polarity
2024-05-31 Add CAN communication for safeties
2024-05-31 Fix connector wiring
2024-05-31 Update can library
2024-06-15 Format the code using clang
2024-06-15 Use FreeRTOS
2024-06-15 Clean up the code
2024-06-15 Fix compilation warning
2024-06-15 Move CAN library to components
2024-06-15 Add interface task
2024-06-15 Move tasks to the separate directory
2024-06-24 Control brake light and RTDS
2024-06-30 Turn on RTD for a specific time
2024-07-01 Add safety task
2024-07-01 Increase the total heap size for FreeRTOS
2024-07-02 Change notification to message instead of the group
2024-07-02 Handle LEDs
2024-07-02 Move tasks to a separate directory
2024-07-06 Add enclosure CAD files
2024-07-06 Add a groove around the edges of the box
2024-07-06 Add a bezel
2024-07-07 Add spacers
2024-07-18 Update schematic to reflect hardware changes
2024-07-22 Acquire data mutex only when needed
2024-08-07 Publish temperature data
2025-07-27 Update the README
